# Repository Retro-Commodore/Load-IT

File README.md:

# Load-it - Azimuth indicator for the Datassette

https://www.lemon64.com/forum/viewtopic.php?t=43257

This is the reverse engineered files provided with permission from e5frog

# What does it do?
it's a pcb which can be attached to the C64 datassette, an indicator shows the azimuth without the need for a program.

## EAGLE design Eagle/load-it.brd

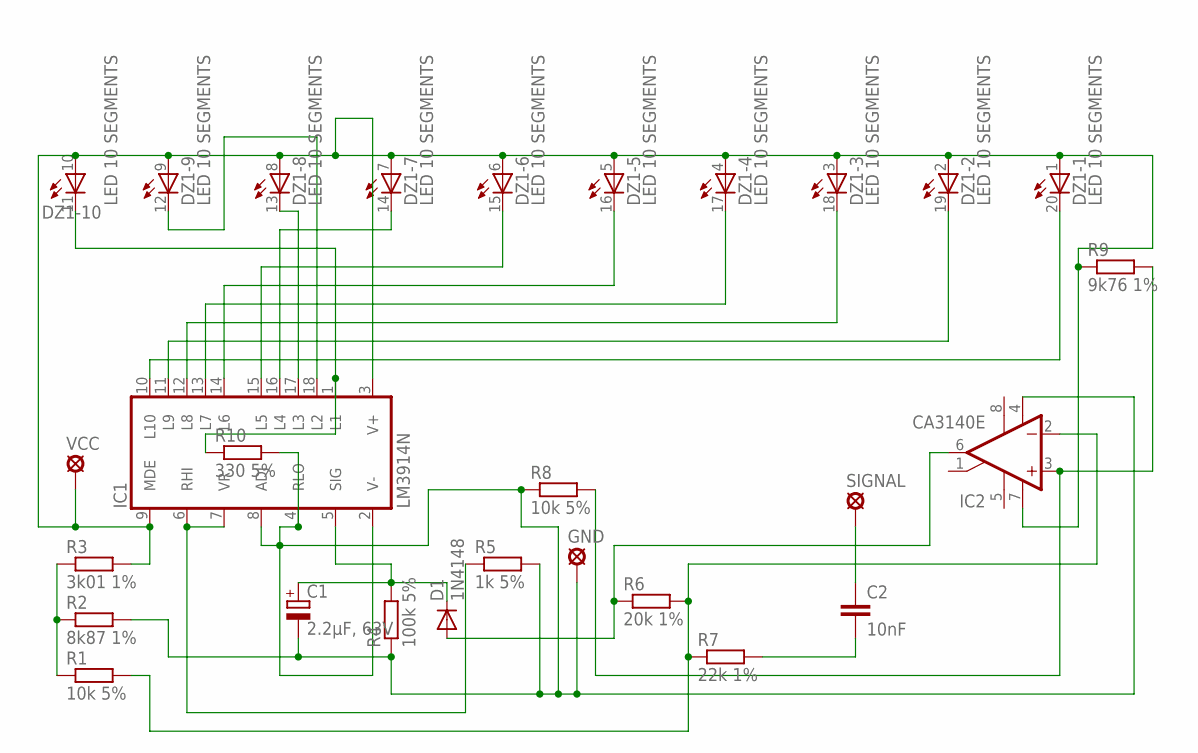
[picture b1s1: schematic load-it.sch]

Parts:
C1: 2.2µF, 63V; E5-6
C2: 10nF; C2.5-2
D1: 1N4148; DO35-7
DZ1: LED 10 SEGMENTS; LB10
GND: GND; LSP10
IC1: LM3914N; DIL18
IC2: CA3140E; DIL08
R1, R8: 10k 5%; 0207/10
R2: 8k87 1%; 0207/10
R3: 3k01 1%; 0207/10
R4: 100k 5%; 0207/10
R5: 1k 5%; 0207/10
R6: 20k 1%; 0207/10
R7: 22k 1%; 0207/10
R9: 9k76 1%; 0207/10
R10: 330 5%; 0207/10
SIGNAL: SG; LSP10
VCC: VCC; LSP10

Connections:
unnamed: DZ1.20 (C), IC1.10 (L10)
unnamed: IC2.2 (-IN), R1.2, R6.2, R7.1
unnamed: D1.A, IC2.6 (OUT), R6.1
unnamed: IC2.3 (+IN), R8.2, R9.2
unnamed: C1.-, GND.MP, IC1.2 (V-), IC1.4 (RLO), IC1.8 (ADJ), IC2.4 (V-), R2.2, R4.1, R5.2, R8.1, R10.2
unnamed: DZ1.1 (A), DZ1.2 (A), DZ1.3 (A), DZ1.4 (A), DZ1.5 (A), DZ1.6 (A), DZ1.7 (A), DZ1.8 (A), DZ1.9 (A), DZ1.10 (A), IC1.3 (V+), IC1.9 (MDE), IC2.7 (V+), R3.2, R9.1, VCC.MP
unnamed: C1.+, D1.C, IC1.5 (SIG), R4.2
unnamed: IC1.6 (RHI), IC1.7 (VR), R5.1
unnamed: DZ1.11 (C), IC1.1 (L1), R10.1
unnamed: DZ1.19 (C), IC1.11 (L9)
unnamed: DZ1.18 (C), IC1.12 (L8)
unnamed: DZ1.17 (C), IC1.13 (L7)
unnamed: DZ1.16 (C), IC1.14 (L6)
unnamed: DZ1.15 (C), IC1.15 (L5)
unnamed: DZ1.14 (C), IC1.16 (L4)
unnamed: DZ1.13 (C), IC1.17 (L3)
unnamed: DZ1.12 (C), IC1.18 (L2)
unnamed: R1.1, R2.1, R3.1
unnamed: C2.2, R7.2
unnamed: C2.1, SIGNAL.MP

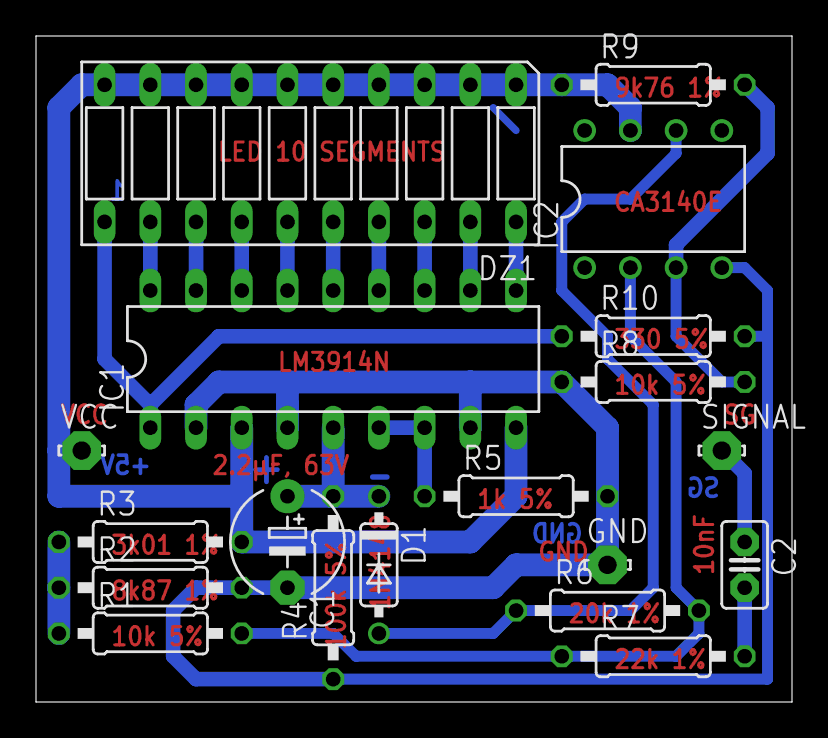
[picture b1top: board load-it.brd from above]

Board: 2 copper layers, 42.0 x 37.0 mm, 19 parts (0 on the bottom side), 20 nets.

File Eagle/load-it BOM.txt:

Partlist exported from D:/ARBEIT/LOAD-IT/load-it.sch at 2014-09-05 11:43:47

Part   Value        Device       Package Description                                           
C1     2.2µF, 6.3V  CPOL-EUE5-6  E5-6    POLARIZED CAPACITOR, European symbol                  
C2     10nF         C2.5/2       C2.5-2  CAPACITOR                                             
D1     1N4148DO35-7 1N4148DO35-7 DO35-7  DIODE                                                 
DZ1    LB10         LB10         LB10    LED BLOCK                                             
GND    LSP10        LSP10        LSP10   SOLDER PAD drill 1.0 mm, distributor Buerklin, 12H555 
IC1    LM3914N      LM3914N      DIL18   LED DRIVER                                            
IC2    CA3140N      CA3140N      DIL08   OP AMP                                                
R1     10k 5%       R-EU_0207/10 0207/10 RESISTOR, European symbol                             
R2     8k87 1%      R-EU_0207/10 0207/10 RESISTOR, European symbol                             
R3     3k01 1%      R-EU_0207/10 0207/10 RESISTOR, European symbol                             
R4     100k 5%      R-EU_0207/10 0207/10 RESISTOR, European symbol                             
R5     1k 5%        R-EU_0207/10 0207/10 RESISTOR, European symbol                             
R6     20k 1%       R-EU_0207/10 0207/10 RESISTOR, European symbol                             
R7     22k 1%       R-EU_0207/10 0207/10 RESISTOR, European symbol                             
R8     10k 5%       R-EU_0207/10 0207/10 RESISTOR, European symbol                             
R9     9k76 1%      R-EU_0207/10 0207/10 RESISTOR, European symbol                             
R10    330 5%       R-EU_0207/10 0207/10 RESISTOR, European symbol                             
SIGNAL LSP10        LSP10        LSP10   SOLDER PAD drill 1.0 mm, distributor Buerklin, 12H555 
VCC    VCC          LSP10        LSP10   SOLDER PAD drill 1.0 mm, distributor Buerklin, 12H555

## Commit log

2024-01-13 Added pictures from forum post
